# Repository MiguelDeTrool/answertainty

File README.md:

# answertainty
Simple Arduino Nano based pseudorandom Eurorack module

Answertainty creates pseudorandom signals. It is inspired by NLC's Sloths, and Bogaudio's Walk. I must warn anyone attempting this that I have not tested these exact PCBs, only an earlier prototype, that I then made minor modifications to for this version. I am quite confident that they will work, and feel free to send me a message if you decide to try this out.

The "Gate" output changes to 0v or 5v randomly. The further the pot is turned right, the more frequently it changes state.

The "Slow" outputs create slowly evolving continuous control voltages, from about -5v to +5v. The further the pot is turned right, the faster it evolves.

The "Fast" output does the same as the "Slow" outputs, but responds to the pot in the opposite direction.

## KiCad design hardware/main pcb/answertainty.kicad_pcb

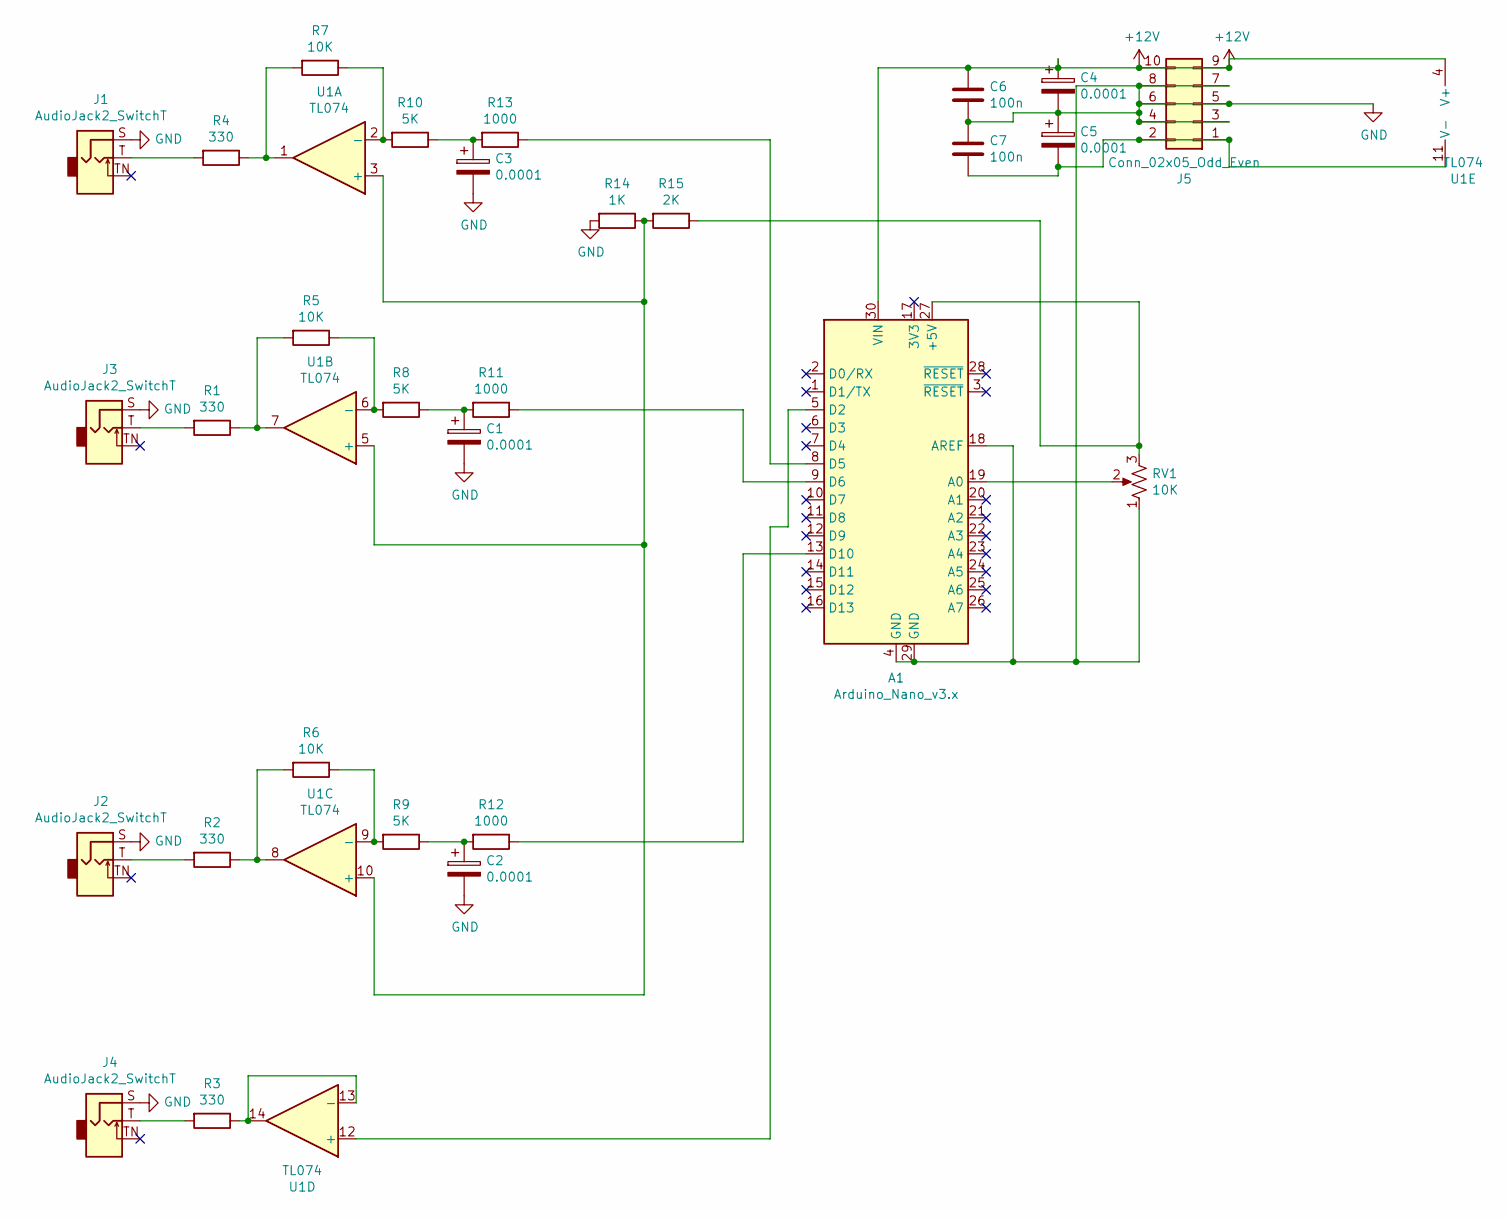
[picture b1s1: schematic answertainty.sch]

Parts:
A1: Arduino_Nano_v3.x; Arduino_Nano
C1, C2, C3, C4, C5: 0.0001; CP_Radial_D6.3mm_P2.50mm
C6, C7: 100n; C_Disc_D3.8mm_W2.6mm_P2.50mm
J1, J2, J3, J4: AudioJack2_SwitchT; PJ302M
J5: Conn_02x05_Odd_Even; PinHeader_2x05_P2.54mm_Vertical
R1, R2, R3, R4: 330; R_Axial_DIN0204_L3.6mm_D1.6mm_P5.08mm_Horizontal
R5, R6, R7: 10K; R_Axial_DIN0204_L3.6mm_D1.6mm_P5.08mm_Horizontal
R8, R9, R10: 5K; R_Axial_DIN0204_L3.6mm_D1.6mm_P5.08mm_Horizontal
R11, R12, R13: 1000; R_Axial_DIN0204_L3.6mm_D1.6mm_P5.08mm_Horizontal
R14: 1K; R_Axial_DIN0204_L3.6mm_D1.6mm_P5.08mm_Horizontal
R15: 2K; R_Axial_DIN0204_L3.6mm_D1.6mm_P5.08mm_Horizontal
RV1: 10K; Potentiometer_Alps_RK163_Single_Horizontal
U1: TL074; DIP-14_W7.62mm_Socket_LongPads

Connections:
+12V: A1.30 (VIN), C4.1, C6.1, J5.9, J5.10, U1.4 (V+)
GND: A1.4 (GND), A1.18 (AREF), A1.29 (GND), C1.2, C2.2, C3.2, C4.2, C5.1, C6.2, C7.1, J1.S, J2.S, J3.S, J4.S, J5.3, J5.4, J5.5, J5.6, J5.7, J5.8, R14.2, RV1.1
unnamed: A1.5 (D2), U1.12 (+)
unnamed: A1.8 (D5), R13.1
unnamed: A1.9 (D6), R11.1
unnamed: A1.13 (D10), R12.1
unnamed: A1.19 (A0), RV1.2
unnamed: A1.27 (+5V), R15.1, RV1.3
unnamed: C1.1, R8.1, R11.2
unnamed: C2.1, R9.1, R12.2
unnamed: C3.1, R10.1, R13.2
unnamed: C5.2, C7.2, J5.1, J5.2, U1.11 (V-)
unnamed: J1.T, R4.2
unnamed: J2.T, R2.2
unnamed: J3.T, R1.2
unnamed: J4.T, R3.2
unnamed: R1.1, R5.2, U1.7
unnamed: R2.1, R6.2, U1.8
unnamed: R3.1, U1.13 (-), U1.14
unnamed: R4.1, R7.2, U1.1
unnamed: R5.1, R8.2, U1.6 (-)
unnamed: R6.1, R9.2, U1.9 (-)
unnamed: R7.1, R10.2, U1.2 (-)
unnamed: R14.1, R15.2, U1.3 (+), U1.5 (+), U1.10 (+)

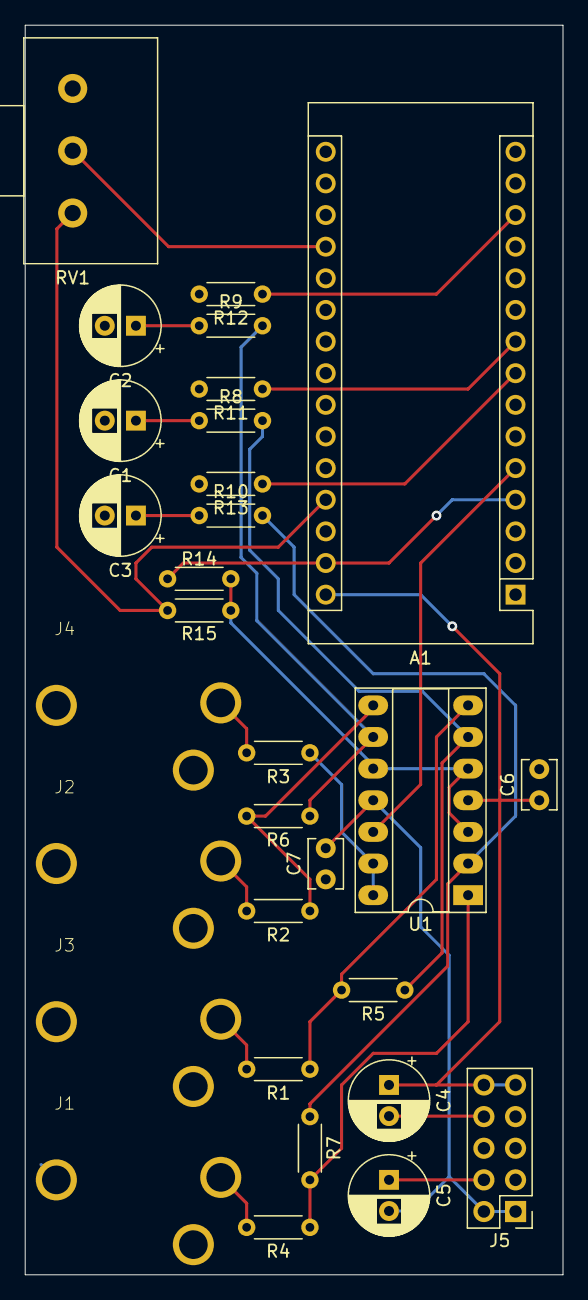
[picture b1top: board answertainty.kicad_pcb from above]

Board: 2 copper layers, 43.2 x 100.3 mm, 30 parts (0 on the bottom side), 24 nets.

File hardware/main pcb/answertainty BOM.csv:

Id	Designator	Package	Quantity	Designation
1	C7,C6	C_Disc_D3.8mm_W2.6mm_P2.50mm	2	100n
2	R7,R6,R5	R_Axial_DIN0204_L3.6mm_D1.6mm_P5.08mm_Horizontal	3	10K
3	J4,J1,J3,J2	PJ302M	4	AudioJack2_SwitchT
4	A1	Arduino_Nano	1	Arduino_Nano_v3.x
5	C4,C5,C3,C2,C1	CP_Radial_D6.3mm_P2.50mm	5	0,0001
6	R15	R_Axial_DIN0204_L3.6mm_D1.6mm_P5.08mm_Horizontal	1	2K
7	R14	R_Axial_DIN0204_L3.6mm_D1.6mm_P5.08mm_Horizontal	1	1K
8	R13,R12,R11	R_Axial_DIN0204_L3.6mm_D1.6mm_P5.08mm_Horizontal	3	1000
9	R10,R9,R8	R_Axial_DIN0204_L3.6mm_D1.6mm_P5.08mm_Horizontal	3	5K
10	R4,R3,R2,R1	R_Axial_DIN0204_L3.6mm_D1.6mm_P5.08mm_Horizontal	4	330
11	J5	PinHeader_2x05_P2.54mm_Vertical	1	IDC 02x05 connector
12	RV1	Potentiometer_Alps_RK163_Single_Horizontal	1	10K
13	U1	DIP-14_W7.62mm_Socket_LongPads	1	TL074

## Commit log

2021-04-21 Update LICENSE
2021-04-21 Create LICENSE
